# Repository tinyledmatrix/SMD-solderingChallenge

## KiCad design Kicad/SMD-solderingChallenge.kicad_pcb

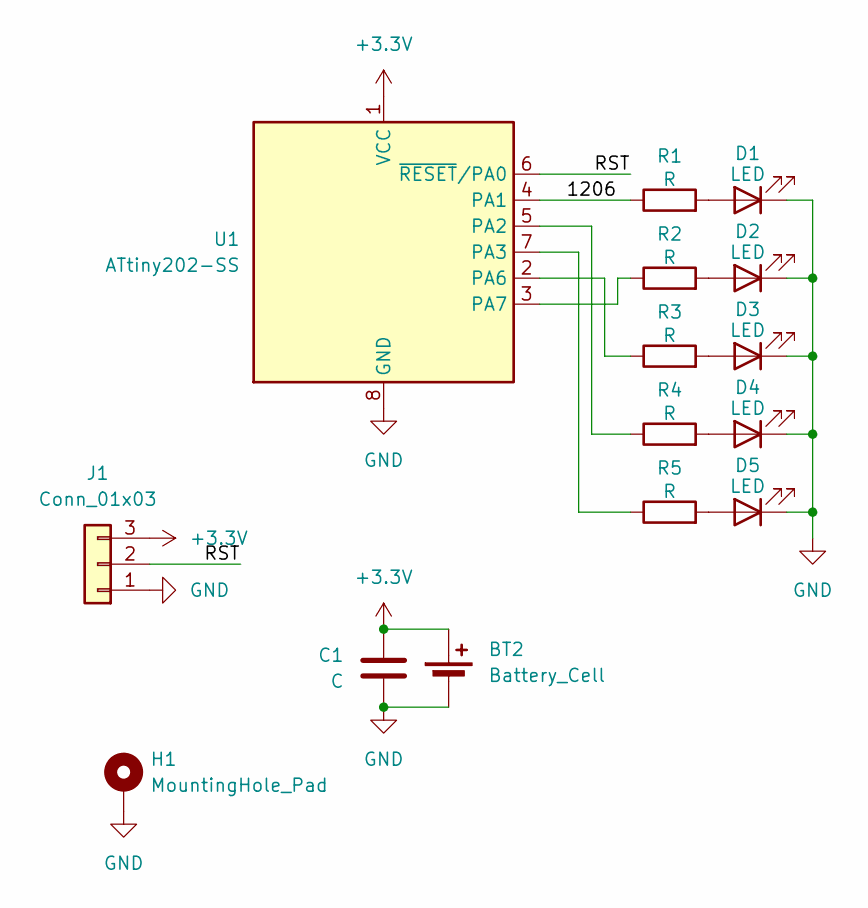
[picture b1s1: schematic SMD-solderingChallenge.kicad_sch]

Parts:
BT2: Battery_Cell; BatteryHolder_Multicomp_BC-2001_1x2032
C1: C; C_0805_2012Metric
D1: LED; LED_1206_3216Metric
D2: LED; LED_0805_2012Metric
D3: LED; LED_0603_1608Metric
D4: LED; LED_0402_1005Metric
D5: LED; LED_0201_0603Metric
H1: MountingHole_Pad; MountingHole_4.3mm_M4_DIN965_Pad
J1: Conn_01x03; PinHeader_1x03_P2.54mm_Vertical
R1: R; R_1206_3216Metric
R2: R; R_0805_2012Metric
R3: R; R_0603_1608Metric
R4: R; R_0402_1005Metric
R5: R; R_0201_0603Metric
U1: ATtiny202-SS; SOIC-8_3.9x4.9mm_P1.27mm

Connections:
+3.3V: BT2.1 (+), C1.1, J1.3, U1.1 (VCC)
/1206: R1.1, U1.4 (PA1)
/RST: J1.2, U1.6 (~RESET/PA0)
GND: BT2.2 (-), C1.2, D1.1 (K), D2.1 (K), D3.1 (K), D4.1 (K), D5.1 (K), H1.1, J1.1, U1.8 (GND)
unnamed: D1.2 (A), R1.2
unnamed: D2.2 (A), R2.2
unnamed: D3.2 (A), R3.2
unnamed: D4.2 (A), R4.2
unnamed: D5.2 (A), R5.2
unnamed: R4.1, U1.5 (PA2)
unnamed: R5.1, U1.7 (PA3)
unnamed: R3.1, U1.2 (PA6)
unnamed: R2.1, U1.3 (PA7)

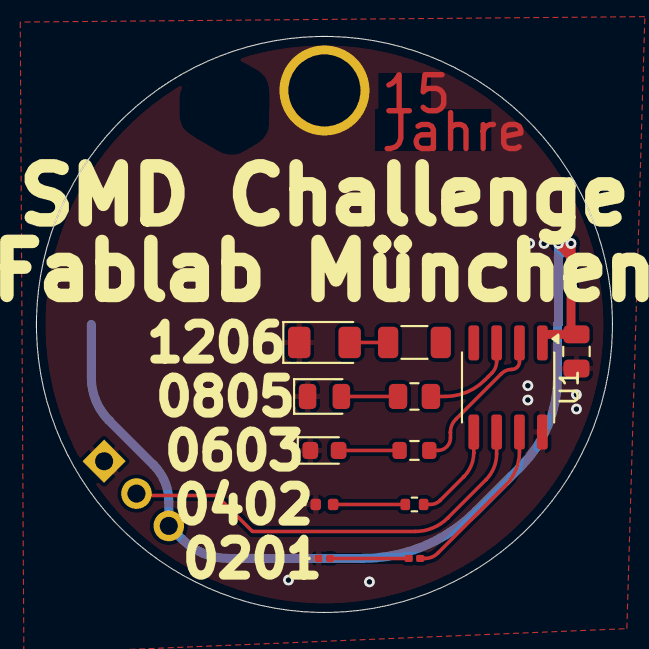
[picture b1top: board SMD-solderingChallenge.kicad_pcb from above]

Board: 2 copper layers, 32.0 x 32.0 mm, 15 parts (1 on the bottom side), 13 nets.

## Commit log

2025-05-18 kicad push first early version
